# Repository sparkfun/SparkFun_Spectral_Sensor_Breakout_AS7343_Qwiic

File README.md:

SparkFun Spectral Sensor - AS7343 (Qwiic)
=========================================

The SparkFun Spectral Sensor Breakout - AS7343 (Qwiic) offers a highly accurate but compact spectral analysis tool for both the visible spectrum and near-infrared. The AS7343 senses light between ~380mn to 1000mn over 14 channels with 11 color bands across the visible spectrum, one near-infrared channel, one clear channel (full sensing spectrum) along with flicker detection. The AS7343 also has an interrupt pin to trigger events based on specific measurements from the sensor as well as a programmable GPIO pin to help synchronize measurements with external devices. This breakout comes standard with a bright white LED for taking measurements but also includes connection points for users who wish to use their own LED if needed.

Repository Contents
-------------------

* **/Documentation** - Data sheets, additional product information
* **/Hardware** - Eagle design files (.brd, .sch)
* **/Production** - Production panel files (.brd)
* **/docs** -  Documentation files for the Spectral UV Sensor
* **/overrides** -  Overrides for GitHub pages content

Documentation
--------------
* **[Arduino Library](https://github.com/sparkfun/SparkFun_AS7343_Arduino_Library/tree/main)** - Arduino library for the Spectral Sensor - AS7343 (Qwiic).
* **[Python Package](https://github.com/sparkfun/qwiic_as7343_py)** - Python package for the Spectral Sensor - AS7343 (Qwiic)
* **[Hookup Guide](https://docs.sparkfun.com/SparkFun_Spectral_Sensor_Breakout_AS7343_Qwiic)** - Basic hookup guide for the Spectral Sensor - AS7343 (Qwiic).

Product Versions
----------------
* [SEN-23220](https://www.sparkfun.com/sparkfun-spectral-sensor-as7343-qwiic.html) - Spectral Sensor - AS7343 (Qwiic)

License Information
-------------------

This product is _**open source**_! 

Please review the LICENSE.md file for license information. 

If you have any questions or concerns on licensing, please contact technical support on our [SparkFun forums](https://forum.sparkfun.com/viewforum.php?f=152).

Distributed as-is; no warranty is given.

- Your friends at SparkFun.

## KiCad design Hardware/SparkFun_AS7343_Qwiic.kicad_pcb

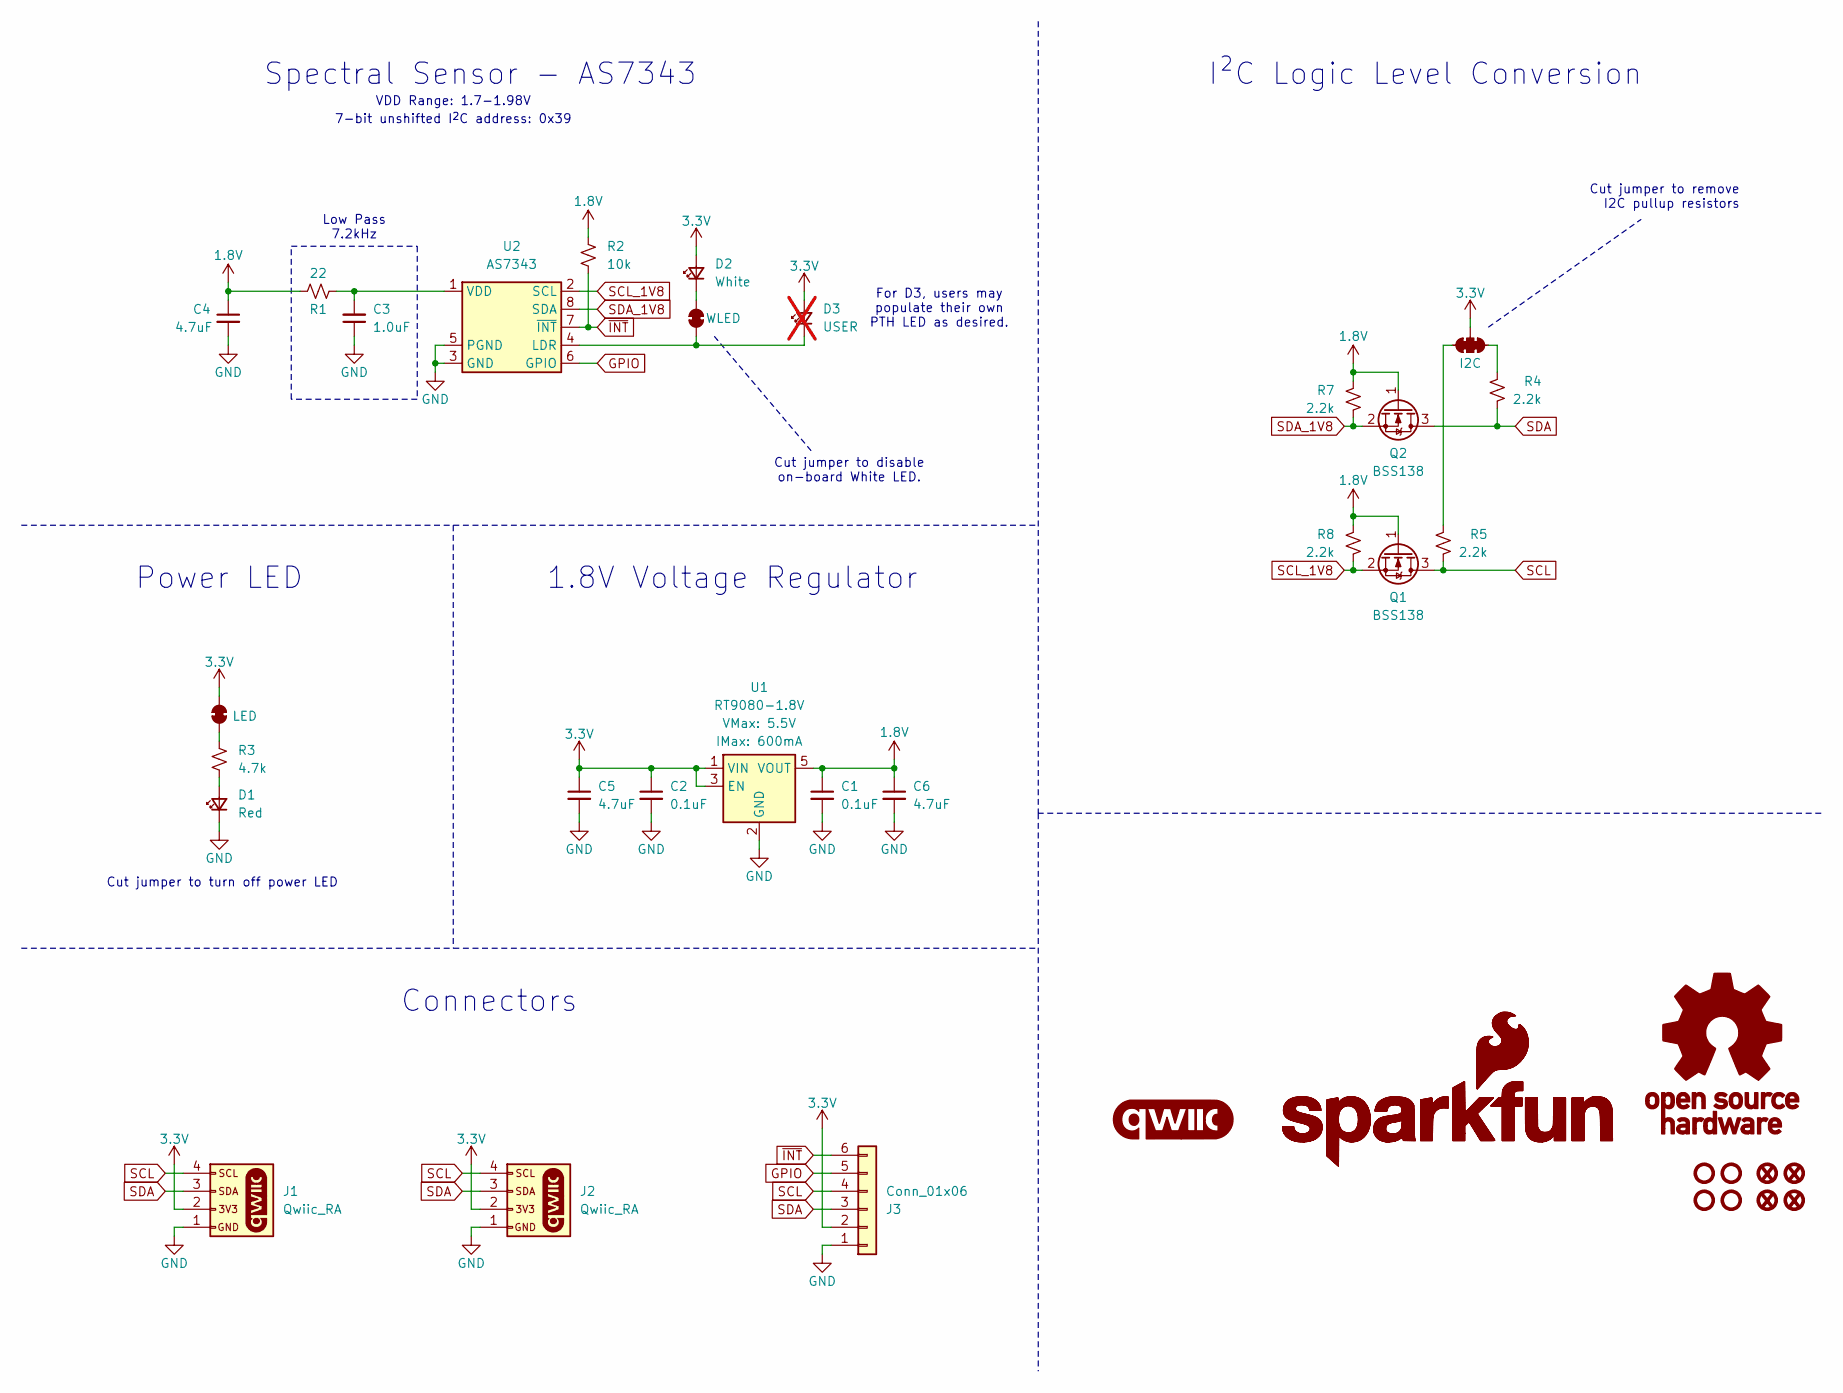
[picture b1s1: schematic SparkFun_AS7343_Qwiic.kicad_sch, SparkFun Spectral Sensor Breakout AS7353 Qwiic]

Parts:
C1, C2: 0.1uF; C_0603_1608Metric; Voltage 25V; Tolerance 20%
C3: 1.0uF; C_0603_1608Metric; Voltage 16V; Tolerance 10%
C4, C5, C6: 4.7uF; C_0603_1608Metric; Voltage 35V; Tolerance 20%
D1: Red; LED_0603_1608Metric_Red
D2: White; LUXEON_3014_SMD_LED
D3: USER; LED_5mm_PTH_Red_NoSilk; not fitted
FID1, FID2, FID3, FID4: Fiducial_0.5mm; Fiducial_0.5mm_Mask1mm
G1: qwiic_Logo
G2: SparkFun_Logo; SparkFun_Logo_8mm
G3: SparkFun_Logo
G4: OSHW_Logo; Creative_Commons_License
J1, J2: Qwiic_RA; JST_SMD_1.0mm-4_Black
J3: Conn_01x06; 1x06
JP1: LED; Jumper_2_NC_Trace
JP2: I2C; Jumper_3_NC-2_Trace
JP3: WLED; Jumper_2_NC_Trace
Q1, Q2: BSS138; SOT23-3
R1: 22; R_0603_1608Metric
R2: 10k; R_0603_1608Metric
R3: 4.7k; R_0603_1608Metric
R4, R5, R7, R8: 2.2k; R_0603_1608Metric
ST1, ST2, ST3, ST4: Standoff
U1: RT9080-1.8V; SOT23-5
U2: AS7343; AMS_OLGA-8_2x3.1mm_P0.8mm

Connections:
1.8V: C1.1, C4.1, C6.1, Q1.1 (G), Q2.1 (G), R1.1, R2.2, R7.1, R8.1, U1.5 (VOUT)
3.3V: C2.1, C5.1, D2.2 (A), D3.2 (A), J1.2, J2.2, J3.2, JP1.2 (B), JP2.2 (B), U1.1 (VIN), U1.3 (EN)
GND: C1.2, C2.2, C3.1, C4.2, C5.2, C6.2, D1.1 (K), J1.1, J2.1, J3.1, U1.2 (GND), U2.3 (GND), U2.5 (PGND)
GPIO: J3.5, U2.6 (GPIO)
unnamed: D1.2 (A), R3.1
unnamed: D2.1 (K), JP3.1 (A)
unnamed: D3.1 (K), JP3.2 (B), U2.4 (LDR)
unnamed: JP1.1 (A), R3.2
unnamed: JP2.1 (A), R5.1
unnamed: JP2.3 (C), R4.2
unnamed: C3.2, R1.2, U2.1 (VDD)
SCL: J1.4, J2.4, J3.4, Q1.3 (D), R5.2
SCL_1V8: Q1.2 (S), R8.2, U2.2 (SCL)
SDA: J1.3, J2.3, J3.3, Q2.3 (D), R4.1
SDA_1V8: Q2.2 (S), R7.2, U2.8 (SDA)
~INT: J3.6, R2.1, U2.7 (~INT)

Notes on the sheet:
Low Pass 7.2kHz
For D3, users may populate their own PTH LED as desired.
Cut jumper to remove I2C pullup resistors
1.8V Voltage Regulator
7-bit unshifted I^{2}C address: 0x39
I²C Logic Level Conversion
Cut jumper to turn off power LED
Cut jumper to disable on-board White LED.
Power LED
VDD Range: 1.7-1.98V
Connectors
Spectral Sensor - AS7343

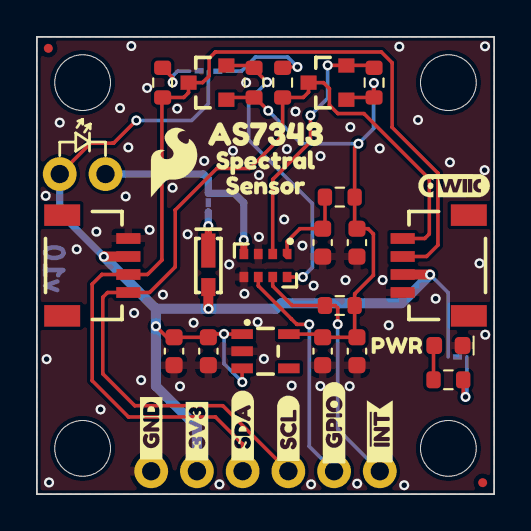
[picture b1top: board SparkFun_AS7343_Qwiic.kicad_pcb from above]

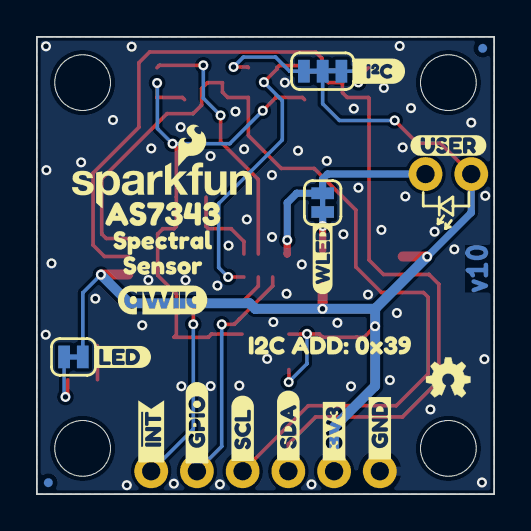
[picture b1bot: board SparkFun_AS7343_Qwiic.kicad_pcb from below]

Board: 2 copper layers, 25.4 x 25.4 mm, 60 parts (20 on the bottom side), 16 nets.

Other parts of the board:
Ref**: Val**; OSHW_Logo_2.5mm
kibuzzard-65A8A8B4: G***; kibuzzard-65A8A8B4
kibuzzard-67BF7CFE: G***; kibuzzard-67BF7CFE
kibuzzard-67BF7F2F: G***; kibuzzard-67BF7F2F
kibuzzard-67BF7F13: G***; kibuzzard-67BF7F13
kibuzzard-67ED66D1, kibuzzard-67ED66D1#2: G***; kibuzzard-67ED66D1
kibuzzard-67ED66F3, kibuzzard-67ED66F3#2: G***; kibuzzard-67ED66F3
kibuzzard-67ED66FD, kibuzzard-67ED66FD#2: G***; kibuzzard-67ED66FD
kibuzzard-67ED691F, kibuzzard-67ED691F#2: G***; kibuzzard-67ED691F
kibuzzard-67ED694E, kibuzzard-67ED694E#2: G***; kibuzzard-67ED694E
kibuzzard-67ED714F: G***; kibuzzard-67ED714F
kibuzzard-67ED716A: G***; kibuzzard-67ED716A
kibuzzard-67ED6905: G***; kibuzzard-67ED6905
kibuzzard-67ED7158: G***; kibuzzard-67ED7158
kibuzzard-67ED7177: G***; kibuzzard-67ED7177
kibuzzard-67ED7915: G***; kibuzzard-67ED7915
kibuzzard-67F027E1: G***; kibuzzard-67F027E1
kibuzzard-67F954F3: G***; kibuzzard-67F954F3
kibuzzard-67F8112D: G***; kibuzzard-67F8112D
kibuzzard-67F81140: G***; kibuzzard-67F81140

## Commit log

2025-04-02 layout pretty much there
2025-04-03 3d models
    -created 3d models for AS7343 and Luxeon 3014
    -add datasheet link to AS7343 symbol
2025-04-03 remove extra directory - resave in kicad 9.0
2025-04-04 PROD_IDs
    -prod IDs for IC and white LED
2025-04-04 datasheet
2025-04-04 low pass filter components moved and re-routed
    -rotated parts so that C3 and C4 have direct GND return paths to IC GND pads (and Vreg GND pads)
2025-04-04 PTH pad LED silk update
    -Added arrows to silk graphics, to clearly show it's an LED (rather than just a diode)
2025-04-04 I2C address in sch and bottom silk
2025-04-04 checklist run eng
    -sch tightening
    -vcc range added to sch
    -removed PROD_ID from DNP LED
    -add 1.8V testpoint
    -increased copper to dimension clearance from 3 mils to 8 mils (avoiding sanding damage)
    -nudged qwiic connectors inward from the edge by 5mils (avoiding sanding damage)
2025-04-04 measures
2025-04-04 move measures to correct layer
2025-04-08 catches in review
    -corrected GPIO and INT silk labels
    -rerouted traces near power LED and R3
    -removed a ground nubbin on pad of C4
2025-04-09 more review catches
    -Checked the properties box for DNP on D3, also exclude from BOM.
    -sch cleanup
    -removed isolation jumper for 1v8 i2c pullups
2025-04-09 reduced paste on IC pads by 10%
2025-04-10 more review notes
    -changed 1V8 to 1.8V to match style of 3.3V
    -corrected schematic note for low pass filter. Is kHz, was KHz
    -removed one of the QWIIC logos
    -Moved OSHW to bottom silk
    -aligned PWR LED silk label exactly with Y val of LED.
    -changed sch note about i2c address to be "7-bit unshifted I2C address: 0x39"
2025-04-10 everything moved to 12.5 mil grid
    -moved all parts to 12.5 mil grid and re-routed as necessary
2025-04-11 eng checklist for protos v01
    -solder mask changed to black for protos
    -DRC exclusions
2025-04-11 added USER LED label to bottom silk
    -changed value ot D3 to "USER"
    -added silk label to bottom for USER LED
2025-04-11 prototype gerbers v01
2025-04-14 library work
    -updated PTH USER LED (DNP) to have fab outline and 3d model link for reference only
2025-04-16 Initial docs commit
    Adding template docs files & base images.
2025-04-21 Assembly sheet v01
    -repositioned values for better assembly sheet
    -screenshot of assembly sheet for v01
2025-04-22 fixed logic level converters
    -body diodes in LLC transistors were allowing high side voltage into low side. (This was incorrect in v01).
    -fixed LLC circuit to have low/high voltages on the correct sides
    -rerouted
    -bumped version to v02
2025-05-05 bumped version to v10 in sch and pcb
2025-05-06 Docs update
    Hookup Guide content update. Adding MicroPython sections & initial docs content commit.
2025-05-06 Minor Docs Update
    Adding overrides folder. Minor additions to several markdown pages for Hookup Guide.
2025-05-07 eng checklist run for v10
    -updated soldermask color to red
    -library update on the DNP 5mm pth LED (linking due to new naming)
    -library update on qwiic connector - looks like just an update on the courtyard
2025-05-07 production panel and gerbers v10
2025-05-19 Docs update
    Update to Arduino section to match latest library release & Quick Start guide update to finalize Arduino portion of the guide.
2025-05-20 Minor docs update
    Adding screenshots for arduino examples & minor updates to software setup & assembly sections.
2025-06-03 Docs photo & initial review update
    Adding photos and board files to assets. General updates to prep for final review.
2025-06-04 Docs final review & publish
    Final review edits to docs files & adding GH pages build files.
2025-06-04 Deployed c6c2ee0 with MkDocs version: 1.6.1
2025-06-06 White Luxeon LED datasheet and power graph
2025-06-06 Deployed ae284ab with MkDocs version: 1.6.1

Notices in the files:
parts and their libraries:
https://creativecommons.org/licenses/by-sa/4.0
Released under the Creative Commons Attribution Share-Alike 4.0 License
